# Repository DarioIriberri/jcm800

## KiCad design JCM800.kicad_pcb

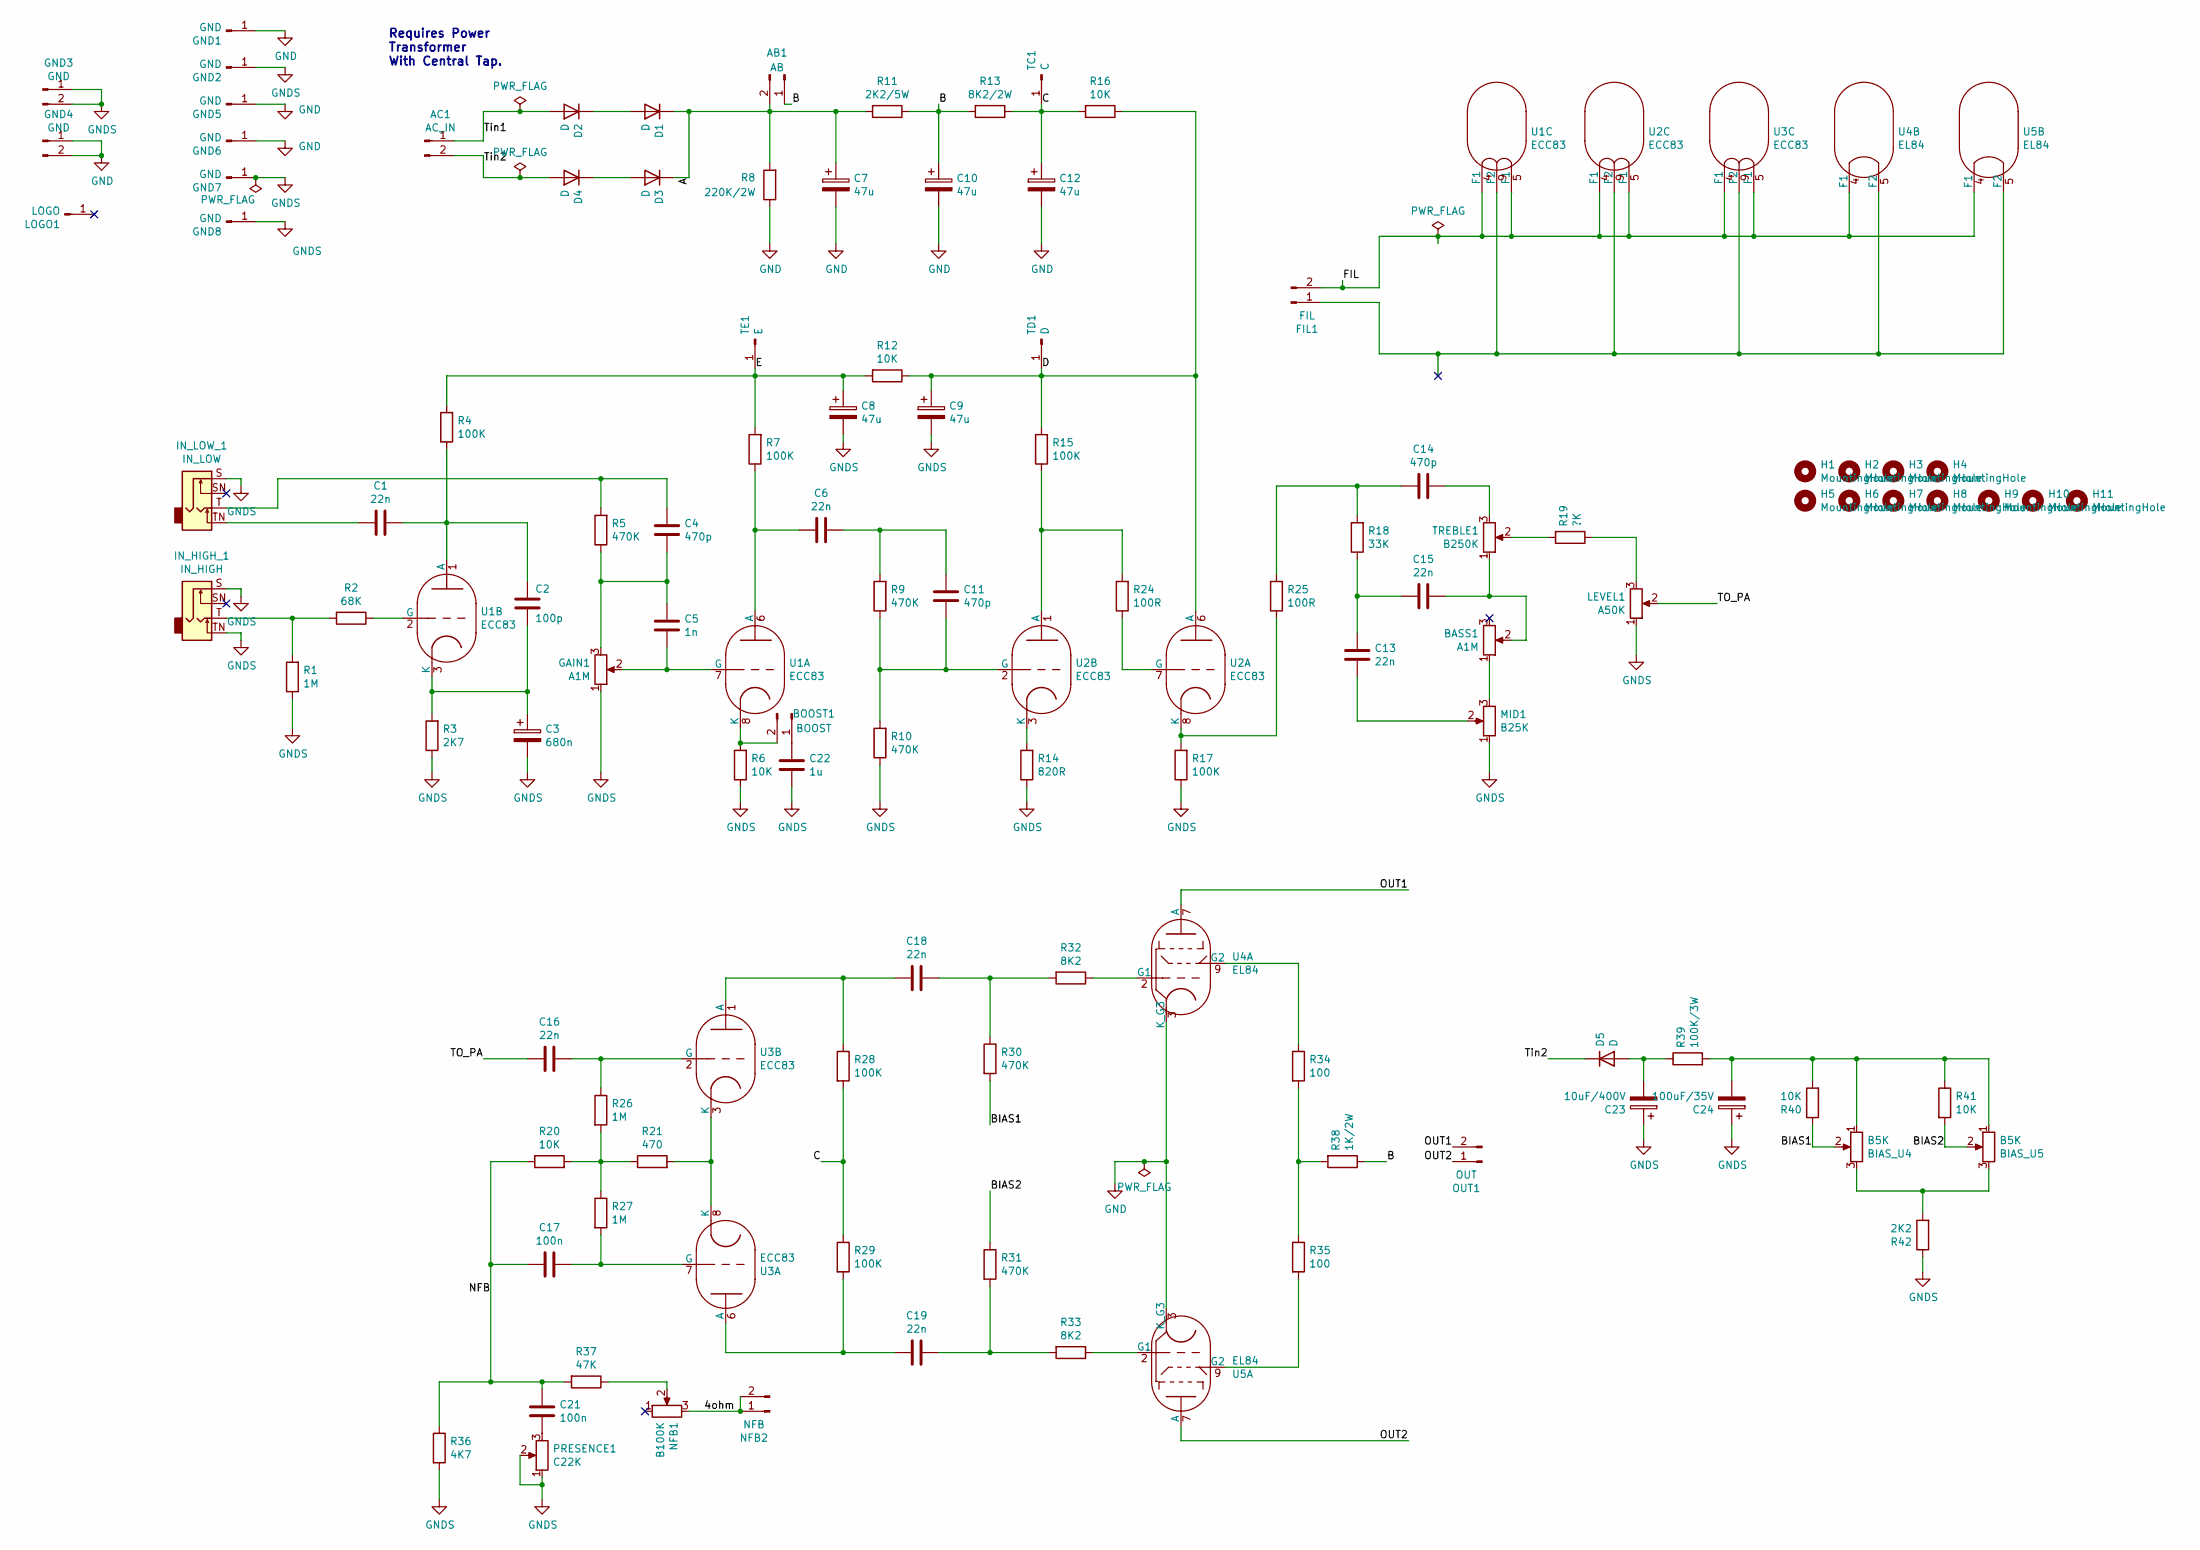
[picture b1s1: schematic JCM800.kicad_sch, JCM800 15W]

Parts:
AB1: AB; TerminalBlock_MetzConnect_Type094_RT03502HBLU_1x02_P5.00mm_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
AC1: AC_IN; TerminalBlock_MetzConnect_Type094_RT03502HBLU_1x02_P5.00mm_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
BASS1: A1M; Potentiometer_Piher_T-16H_Single_Horizontal
BIAS_U4, BIAS_U5: B5K; Potentiometer_Bourns_3296W_Vertical
BOOST1: BOOST; TerminalBlock_MetzConnect_Type094_RT03502HBLU_1x02_P5.00mm_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
C1, C6, C13, C15, C16, C18, C19: 22n; C_Rect_L10.3mm_W5.0mm_P7.50mm_MKS4
C2: 100p; C_Disc_D5.0mm_W2.5mm_P5.00mm
C3: 680n; C_Rect_L10.3mm_W5.0mm_P7.50mm_MKS4
C4: 470p; C_Disc_D5.0mm_W2.5mm_P5.00mm
C5: 1n; C_Rect_L7.0mm_W3.5mm_P5.00mm
C7, C8, C9, C10, C12: 47u; CP_Radial_D18.0mm_P7.50mm
C11: 470p; C_Rect_L7.0mm_W3.5mm_P5.00mm
C14: 470p; C_Rect_L10.0mm_W4.0mm_P7.50mm_FKS3_FKP3
C17, C21: 100n; C_Rect_L10.3mm_W5.0mm_P7.50mm_MKS4
C22: 1u; C_Rect_L7.0mm_W3.5mm_P5.00mm
C23: 10uF/400V; CP_Radial_D10.0mm_P5.00mm
C24: 100uF/35V; CP_Radial_D8.0mm_P3.50mm
D1, D2, D3, D4, D5: D; D_A-405_P10.16mm_Horizontal
FIL1: FIL; TerminalBlock_MetzConnect_Type094_RT03502HBLU_1x02_P5.00mm_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
GAIN1: A1M; Potentiometer_Piher_T-16H_Single_Horizontal
GND1, GND2, GND5, GND6, GND7, GND8: GND; PinHeader_1x01_P2.54mm_Vertical
GND3, GND4: GND; TerminalBlock_MetzConnect_Type094_RT03502HBLU_1x02_P5.00mm_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
H1, H2, H3, H4, H5, H6, H7, H8, H9, H10, H11: MountingHole; MountingHole_3.2mm_M3
IN_HIGH_1: IN_HIGH; 6.35MM_STEREO_SWITCHED_JACK
IN_LOW_1: IN_LOW; 6.35MM_STEREO_SWITCHED_JACK
LEVEL1: A50K; Potentiometer_Piher_T-16H_Single_Horizontal
LOGO1: LOGO; toad-big
MID1: B25K; Potentiometer_Piher_T-16H_Single_Horizontal
NFB1: B100K; Potentiometer_Piher_T-16H_Single_Horizontal
NFB2: NFB; TerminalBlock_MetzConnect_Type094_RT03502HBLU_1x02_P5.00mm_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
OUT1: OUT; TerminalBlock_MetzConnect_Type094_RT03502HBLU_1x02_P5.00mm_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
PRESENCE1: C22K; Potentiometer_Piher_T-16H_Single_Horizontal
R1, R26, R27: 1M; R_Axial_DIN0207_L6.3mm_D2.5mm_P10.16mm_Horizontal
R2: 68K; R_Axial_DIN0207_L6.3mm_D2.5mm_P10.16mm_Horizontal
R3: 2K7; R_Axial_DIN0207_L6.3mm_D2.5mm_P10.16mm_Horizontal
R4, R7, R15, R17, R28, R29: 100K; R_Axial_DIN0207_L6.3mm_D2.5mm_P10.16mm_Horizontal
R5, R9, R10, R30, R31: 470K; R_Axial_DIN0207_L6.3mm_D2.5mm_P10.16mm_Horizontal
R6, R12, R16, R20, R40, R41: 10K; R_Axial_DIN0207_L6.3mm_D2.5mm_P10.16mm_Horizontal
R8: 220K/2W; R_Axial_DIN0414_L11.9mm_D4.5mm_P15.24mm_Horizontal
R11: 2K2/5W; R_Axial_DIN0922_L20.0mm_D9.0mm_P7.62mm_Vertical
R13: 8K2/2W; R_Axial_DIN0414_L11.9mm_D4.5mm_P15.24mm_Horizontal
R14: 820R; R_Axial_DIN0207_L6.3mm_D2.5mm_P10.16mm_Horizontal
R18: 33K; R_Axial_DIN0207_L6.3mm_D2.5mm_P10.16mm_Horizontal
R19: ?K; R_Axial_DIN0207_L6.3mm_D2.5mm_P10.16mm_Horizontal
R21: 470; R_Axial_DIN0207_L6.3mm_D2.5mm_P10.16mm_Horizontal
R24, R25: 100R; R_Axial_DIN0207_L6.3mm_D2.5mm_P10.16mm_Horizontal
R32, R33: 8K2; R_Axial_DIN0207_L6.3mm_D2.5mm_P10.16mm_Horizontal
R34, R35: 100; R_Axial_DIN0207_L6.3mm_D2.5mm_P10.16mm_Horizontal
R36: 4K7; R_Axial_DIN0207_L6.3mm_D2.5mm_P10.16mm_Horizontal
R37: 47K; R_Axial_DIN0207_L6.3mm_D2.5mm_P10.16mm_Horizontal
R38: 1K/2W; R_Axial_DIN0414_L11.9mm_D4.5mm_P15.24mm_Horizontal
R39: 100K/3W; R_Axial_DIN0414_L11.9mm_D4.5mm_P15.24mm_Horizontal
R42: 2K2; R_Axial_DIN0207_L6.3mm_D2.5mm_P10.16mm_Horizontal
TC1: C; PinHeader_1x01_P2.54mm_Vertical
TD1: D; PinHeader_1x01_P2.54mm_Vertical
TE1: E; PinHeader_1x01_P2.54mm_Vertical
TREBLE1: B250K; Potentiometer_Piher_T-16H_Single_Horizontal
U1, U2, U3: ECC83; NOVAL
U4, U5: EL84; NOVAL

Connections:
/4ohm: NFB1.3, NFB2.1, NFB2.2
/A: AB1.2, C7.1, D1.1 (K), D3.1 (K), R8.2, R11.2
/B: AB1.1, C10.1, R11.1, R13.2, R38.1
/BIAS1: BIAS_U4.2, R30.2, R40.1
/BIAS2: BIAS_U5.2, R31.1, R41.2
/C: C12.1, R13.1, R16.2, R28.2, R29.1, TC1.1
/D: C9.1, R12.1, R15.2, R16.1, TD1.1, U2.6 (A)
/E: C8.1, R4.2, R7.2, R12.2, TE1.1
/FIL: FIL1.2, U1.4 (F1), U1.5 (F1), U2.4 (F1), U2.5 (F1), U3.4 (F1), U3.5 (F1), U4.4 (F1), U5.4 (F1)
/NFB: C17.2, C21.2, R20.1, R36.1, R37.2
/OUT1: OUT1.2, U4.7 (A)
/OUT2: OUT1.1, U5.7 (A)
/TO_PA: C16.2, LEVEL1.2
/Tin1: AC1.1, D2.2 (A)
/Tin2: AC1.2, D4.2 (A), D5.1 (K)
GND: C7.2, C10.2, C12.2, GND1.1, GND4.1, GND4.2, GND5.1, GND6.1, R8.1, U4.3 (K_G3), U5.3 (K_G3)
GNDS: C3.2, C8.2, C9.2, C22.2, C23.1, C24.1, GAIN1.1, GND2.1, GND3.1, GND3.2, GND7.1, GND8.1, IN_HIGH_1.S, IN_HIGH_1.TN, IN_LOW_1.S, LEVEL1.1, MID1.1, PRESENCE1.1, PRESENCE1.2, R1.1, R3.1, R6.1, R10.1, R14.1, R17.1, R36.2, R42.1
unnamed: BASS1.1, MID1.3
unnamed: BASS1.2, C15.1, TREBLE1.1
unnamed: BIAS_U4.1, BIAS_U5.1, C24.2, R39.2, R40.2, R41.1
unnamed: BIAS_U4.3, BIAS_U5.3, R42.2
unnamed: BOOST1.1, C22.1
unnamed: BOOST1.2, R6.2, U1.8 (K)
unnamed: C1.2, IN_LOW_1.TN
unnamed: C4.1, IN_LOW_1.T, R5.2
unnamed: C4.2, C5.1, GAIN1.3, R5.1
unnamed: C6.1, C11.1, R9.2
unnamed: C13.1, C15.2, R18.1
unnamed: C13.2, MID1.2
unnamed: C14.1, TREBLE1.3
unnamed: C14.2, R18.2, R25.2
unnamed: C18.1, R30.1, R32.2
unnamed: C19.1, R31.2, R33.2
unnamed: C21.1, PRESENCE1.3
unnamed: D1.2 (A), D2.1 (K)
unnamed: D3.2 (A), D4.1 (K)
unnamed: C23.2, D5.2 (A), R39.1
unnamed: IN_HIGH_1.T, R1.2, R2.2
unnamed: LEVEL1.3, R19.1
unnamed: NFB1.2, R37.1
unnamed: R19.2, TREBLE1.2
unnamed: R20.2, R21.1, R26.2, R27.1
unnamed: R34.2, R35.1, R38.2
unnamed: C6.2, R7.1, U1.6 (A)
unnamed: C5.2, GAIN1.2, U1.7 (G)
unnamed: C1.1, C2.1, R4.1, U1.1 (A)
unnamed: R2.1, U1.2 (G)
unnamed: C2.2, C3.1, R3.2, U1.3 (K)
unnamed: R24.1, U2.7 (G)
unnamed: R17.2, R25.1, U2.8 (K)
unnamed: R15.1, R24.2, U2.1 (A)
unnamed: C11.2, R9.1, R10.2, U2.2 (G)
unnamed: R14.2, U2.3 (K)
unnamed: C19.2, R29.2, U3.6 (A)
unnamed: C17.1, R27.2, U3.7 (G)
unnamed: R21.2, U3.3 (K), U3.8 (K)
unnamed: C18.2, R28.1, U3.1 (A)
unnamed: C16.1, R26.1, U3.2 (G)
unnamed: R32.1, U4.2 (G1)
unnamed: R34.1, U4.9 (G2)
unnamed: R33.1, U5.2 (G1)
unnamed: R35.2, U5.9 (G2)

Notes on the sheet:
Requires Power Transformer With Central Tap.

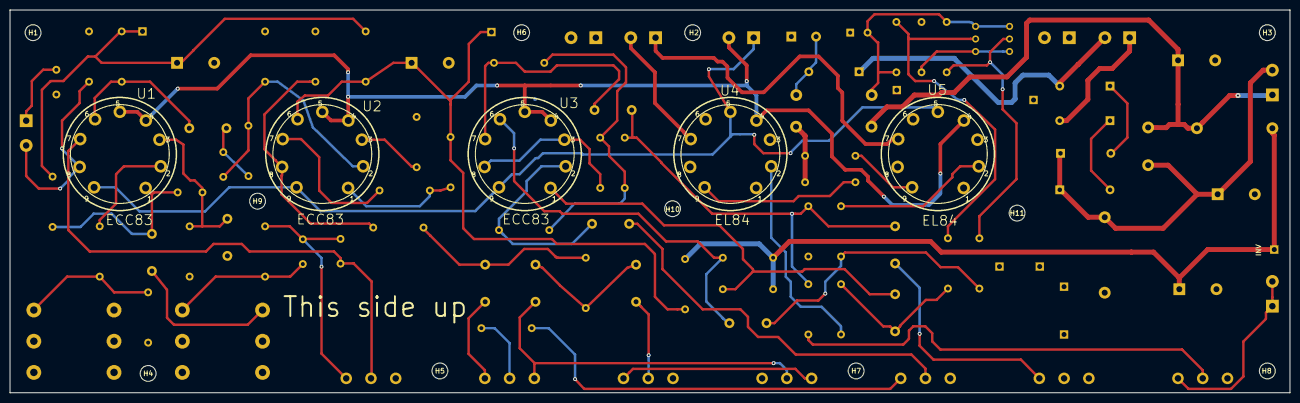
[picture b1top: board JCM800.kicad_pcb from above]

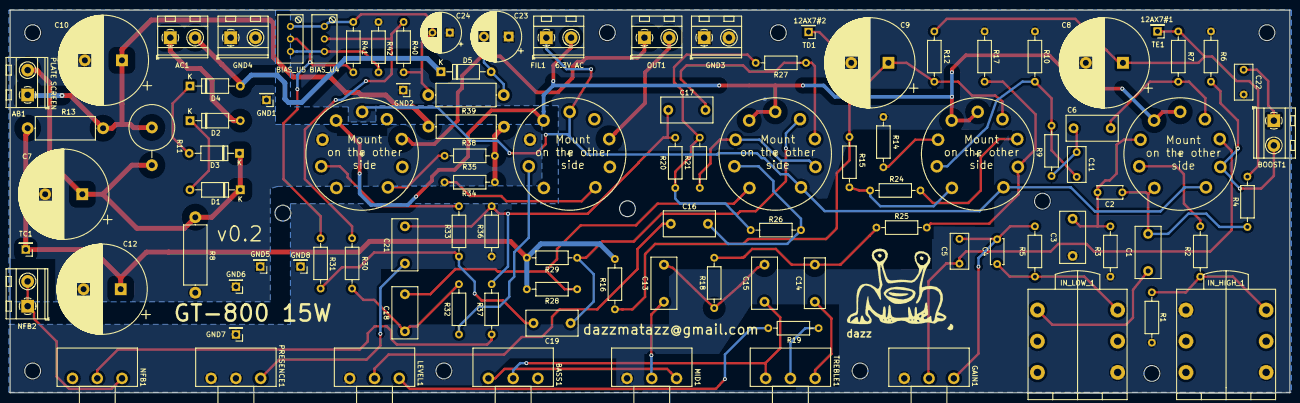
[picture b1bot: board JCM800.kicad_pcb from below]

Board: 2 copper layers, 258.5 x 77.3 mm, 113 parts (97 on the bottom side), 62 nets.

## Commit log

2019-11-30 Cleanup
2019-11-30 Preparing v0.2
2019-12-01 12.6V branch creation.
2019-12-01 Tweaks
2019-12-02 Readme added
2019-12-04 Push-Pull branch
2019-12-04 Preparing initial release
2019-12-04 Added attenuation resistor
2019-12-04 Beef up filter and bias resistors
2019-12-05 New grounding scheme
2019-12-06 Gain trace shielded
2019-12-06 Pics
2019-12-06 Screen resistor added
2019-12-07 Added Johnston's toad logo
2019-12-07 Logo
2019-12-08 Fixed bias
2019-12-09 Test points added. Trimmers moved further away from pentode.
2019-12-09 Metal film resistors
2019-12-09 demo-pp
2019-12-11 Gerbers
2019-12-22 Inverted tubes
2019-12-22 Tubes up
2019-12-22 Preparing 0.2
2019-12-23 Caps spacing
2020-08-11 Added Interactive HTML BOM
2020-08-13 Copper pour to the bottom layer
2020-09-02 6.3V Push-Pull version
2020-09-02 EL84 filament wiring fixed
2020-09-02 6.3V Push-Pull 6N2P branch
2020-09-07 Added voltage elevator for filaments.
2020-09-09 Changed bias voltage source to HV AC
2020-11-19 BOM and other stuff.
2021-01-12 GIT upgrade Test
2022-04-21 Fixed bias config
2022-04-21 Fixed error in bias circuit
2022-04-22 Taking the bias voltage from the HV transformer (requires transformer with central tap connected to GND)
2022-05-15 Fixed bias circuit
2024-06-27 Schematic
2024-07-10 BOM and schematic
2024-07-10 BOM, schematic and gerbers
2024-07-11 3D Render
2026-04-29 Readme
2026-05-02 Floating Filaments on pins 9 for triodes and 5 for pentodes
